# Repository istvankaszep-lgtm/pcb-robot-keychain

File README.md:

# pcb-robot-keychain
This is a robot-shaped PCB keychain. It's a realy cool key chain to put on your backpack, keys and more. I made this proiect for hackclub half life. this is cool keychain, it's shaped like a robot and when you/someone pushes the button on it the eyes(led's) light's up. Also to assemple it, you gonna need soldering iron, solde and flux. when you finished the soldering you need to upload the firmware, actualy there is no firmware for this, i only made the file because the system wanted it. I made this pcb in kicad, first the schematic then the routing and then the desing. I chose this proiect because it was easy to make and solder it.

<table>
  <thead>
    <tr>
      <th>Part</th>
      <th>What it's for</th>
      <th>Qty</th>
      <th>Unit</th>
      <th>Total</th>
      <th>Vendor</th>
    </tr>
  </thead>
  <tbody>
    <tr>
      <td><b>PCB</b></td>
      <td>Robot Keychain PCB manufacturing</td>
      <td>1</td>
      <td>$8.60</td>
      <td>$8.60</td>
      <td><a href="https://jlcpcb.com">JLCPCB</a></td>
    </tr>
    <tr>
      <td><b>Red THT led</b></td>
      <td>Robot's eyes</td>
      <td>2</td>
      <td>$0.06</td>
      <td>$0.12</td>
      <td><a href="https://optimusdigital.ro">Optimus Digital</a></td>
    </tr>
    <tr>
      <td><b>Cr2032</b></td>
      <td>Battery holder</td>
      <td>2</td>
      <td>$0.21</td>
      <td>$0.42</td>
      <td><a href="https://optimusdigital.ro">Optimus Digital</a></td>
    </tr>
    <tr>
      <td><b>Button</b></td>
      <td>Power toggle switch</td>
      <td>1</td>
      <td>$0.09</td>
      <td>$0.09</td>
      <td><a href="https://optimusdigital.ro">Optimus Digital</a></td>
    </tr>
    <tr>
      <td><b>Parts subtotal</b></td>
      <td>—</td>
      <td>—</td>
      <td>—</td>
      <td><b>$0,64</b></td>
      <td>—</td>
    </tr>
    <tr>
      <td><b>Tax & shipping</b></td>
      <td>PCB printing, shipping & parts delivery</td>
      <td>—</td>
      <td>—</td>
      <td><b>$35.07</b></td>
      <td>—</td>
    </tr>
    <tr>
      <td><b>Total</b></td>
      <td>—</td>
      <td>—</td>
      <td>—</td>
      <td><b>$35.71</b></td>
      <td>—</td>
    </tr>
  </tbody>
</table>

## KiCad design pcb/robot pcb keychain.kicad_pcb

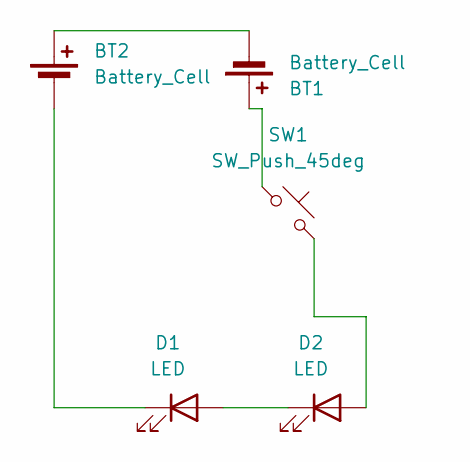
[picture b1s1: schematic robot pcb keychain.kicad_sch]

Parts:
BT1, BT2: Battery_Cell; BatteryHolder_Keystone_3002_1x2032
D1, D2: LED; LED_D4.0mm
SW1: SW_Push_45deg; SW_PUSH_6mm

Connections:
unnamed: BT1.1 (+), SW1.1
unnamed: BT1.2 (-), BT2.1 (+)
unnamed: BT2.2 (-), D1.1 (K)
unnamed: D1.2 (A), D2.1 (K)
unnamed: D2.2 (A), SW1.2

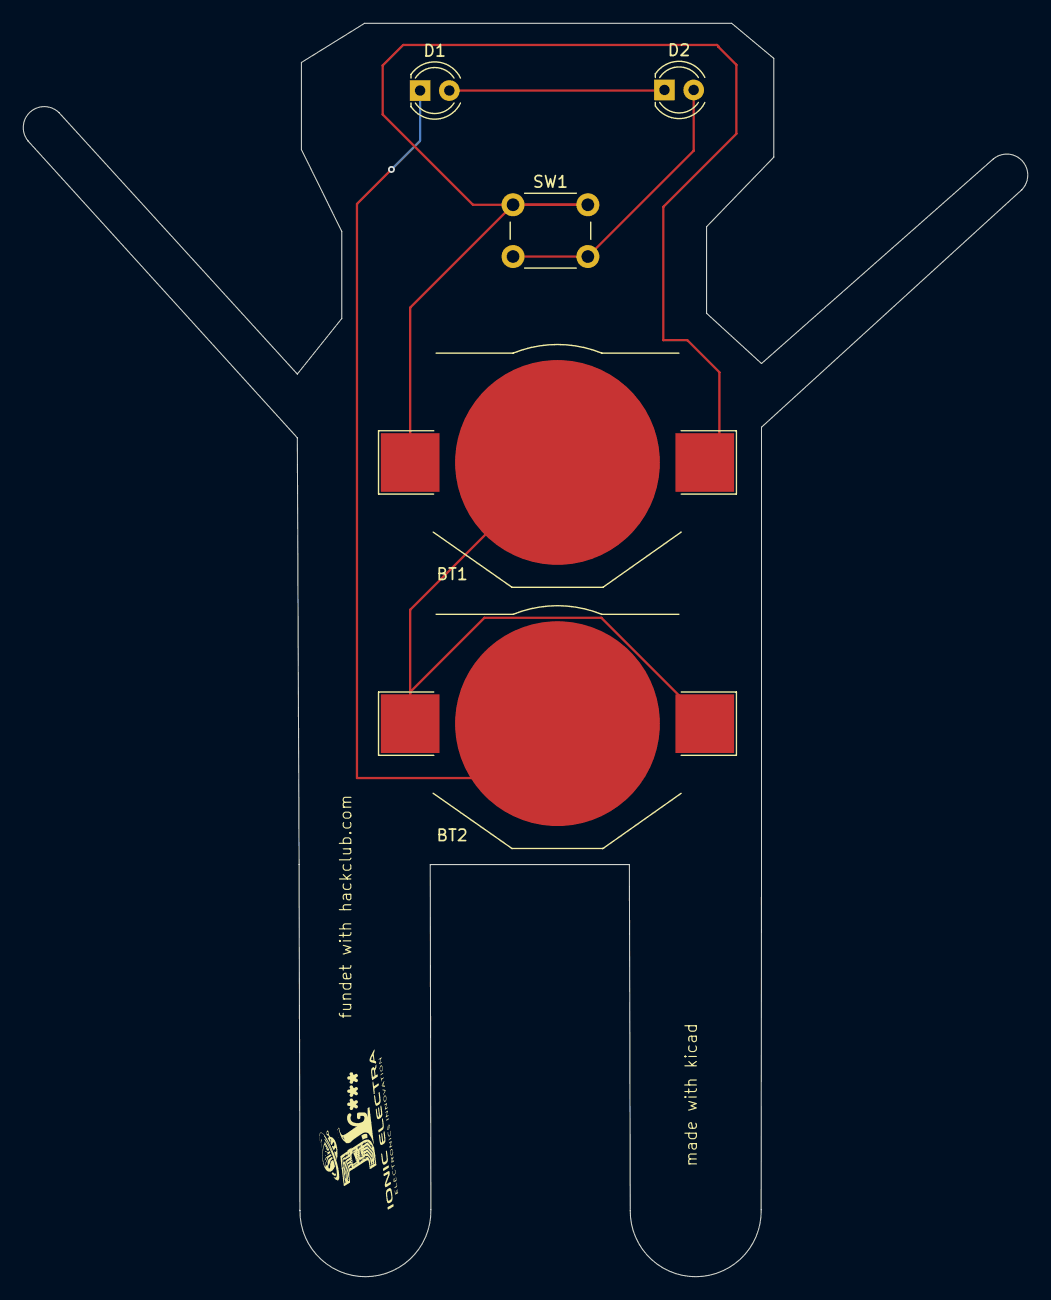
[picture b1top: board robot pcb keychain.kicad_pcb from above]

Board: 2 copper layers, 87.3 x 108.9 mm, 5 parts (0 on the bottom side), 5 nets.
